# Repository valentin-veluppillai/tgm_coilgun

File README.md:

# tgm_coilgun
Coilgun (or magnetic accelerator) built at tgm, for educational purposes
## software used
* processing - used for coding the UI
* kiCad - schematic and layout design
* avrstudio - programming of the microcontroller
## user interface
Written in Java/processing using the controlp5 library. The computer running
the UI communicates with the mincontroller via USART. The UI allows the user to
specify the timing of the coil power supplies.

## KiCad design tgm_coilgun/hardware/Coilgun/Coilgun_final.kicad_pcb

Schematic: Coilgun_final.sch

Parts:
C1, C2: 16pF; CP_Radial_D5.0mm_P2.50mm
C3: xF; CP_Radial_D5.0mm_P2.50mm
F1: FTDI
J1, J3, J4, J5, J6, J7: ST; ScrewTerminal
J2: ISP_HEADER
M1, M2, M3: L6115; Multiwatt-15
R1: 1k; R_Axial_DIN0207_L6.3mm_D2.5mm_P10.16mm_Horizontal
S1: LightSensor
U1: ATMEGA8535-16PU; DIP-40_0_ELL
Y1: 16MHz; QuarzCrystal

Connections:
/COIL_1: J1.1, J1.2, M1.1 (S1), M1.3 (S2), M1.13 (S3), M1.15 (S4)
/COIL_2: J3.1, J3.2, M2.1 (S1), M2.3 (S2), M2.13 (S3), M2.15 (S4)
/COIL_3: J4.1, J4.2, M3.1 (S1), M3.3 (S2), M3.13 (S3), M3.15 (S4)
/MISO: J2.1, U1.7
/MOSFET_EN: M1.6 (EN), M2.6 (EN), M3.6 (EN), R1.1, U1.33
/MOSI: J2.4, U1.6
/RESET: J2.5, U1.9
/SCK: J2.3, U1.8
/VCC_COIL: J5.1, J5.2, M1.2 (D1), M1.4 (D2), M1.12 (D3), M1.14 (D4), M2.2 (D1), M2.4 (D2), M2.12 (D3), M2.14 (D4), M3.2 (D1), M3.4 (D2), M3.12 (D3), M3.14 (D4)
/VCC_MCU: C3.2, J2.2, J6.1, U1.10, U1.30, U1.32
/VCC_MOSFET: J6.2, M1.5 (VCC), M2.5 (VCC), M3.5 (VCC)
GND: C1.2, C2.2, C3.1, F1.9 (GND), F1.16 (GND), J2.6, J7.1, J7.2, M1.8 (GND), M2.8 (GND), M3.8 (GND), R1.2, U1.11, U1.31
unnamed: C1.1, U1.12, Y1.1
unnamed: C2.1, U1.13, Y1.2
unnamed: F1.10 (TXD), U1.14
unnamed: F1.14 (RXD), U1.15
unnamed: M1.7 (IN1), M1.9 (IN2), M1.10 (IN3), M1.11 (IN4), U1.40
unnamed: M2.7 (IN1), M2.9 (IN2), M2.10 (IN3), M2.11 (IN4), U1.39
unnamed: M3.7 (IN1), M3.9 (IN2), M3.10 (IN3), M3.11 (IN4), U1.38
unnamed: S1.1 (DATA1), U1.16
unnamed: S1.2 (DATA2), U1.17

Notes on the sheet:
Higher Voltage and Current Containment This is connected separately
Low Voltage and Current containment Not dangerous

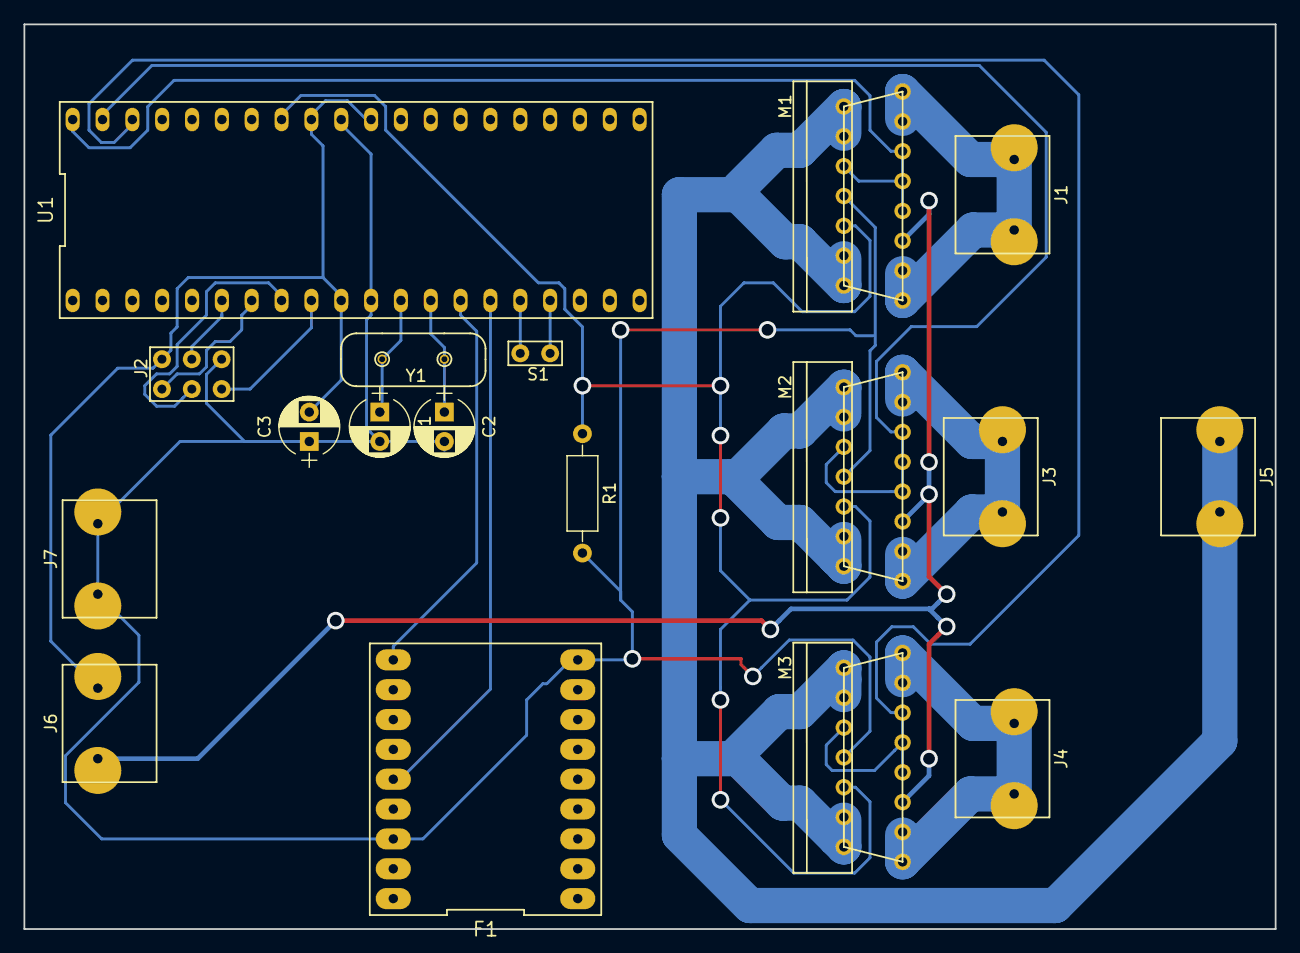
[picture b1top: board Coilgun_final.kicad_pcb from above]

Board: 2 copper layers, 106.5 x 77.0 mm, 18 parts (0 on the bottom side), 21 nets.

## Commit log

2017-12-19 Add files via upload
    uploaded pre-github files
2017-12-20 Updated Schematic and Layout
2017-12-22 cleaned up code for ui - added proper comments - renamed a few variables - removed redundant variables
2017-12-22 fixed markdown mistake
2017-12-22 added changelog
2017-12-22 arduino stuff not needed
2017-12-22 sounds are not used
2017-12-22 housekeeping
2018-01-09 undo
2018-01-09 Added uC-Code
2018-01-09 try again
2018-01-09 add uc code
2018-01-09 Update README.md
    fixed typo
2018-01-09 updated readme and changelog
2018-01-09 updated comments
2018-01-10 changed uCode and Changelog
